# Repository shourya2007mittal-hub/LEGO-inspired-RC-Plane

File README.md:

# LEGO-inspired-RC-Plane

I made an single motor RC tailless aircraft with a custom flight controller based on STM32. It is based on STM32 and end design will be inspired by LEGO.

## Features

Microcontroller: STM32F401CBUx<br>
IMU Sensor: MPU-6050 <br>
Barometer: BMP280<br>
Design inspired by LEGO<br

 ## Schematic & PCB<br>

 # 3d Render<br>

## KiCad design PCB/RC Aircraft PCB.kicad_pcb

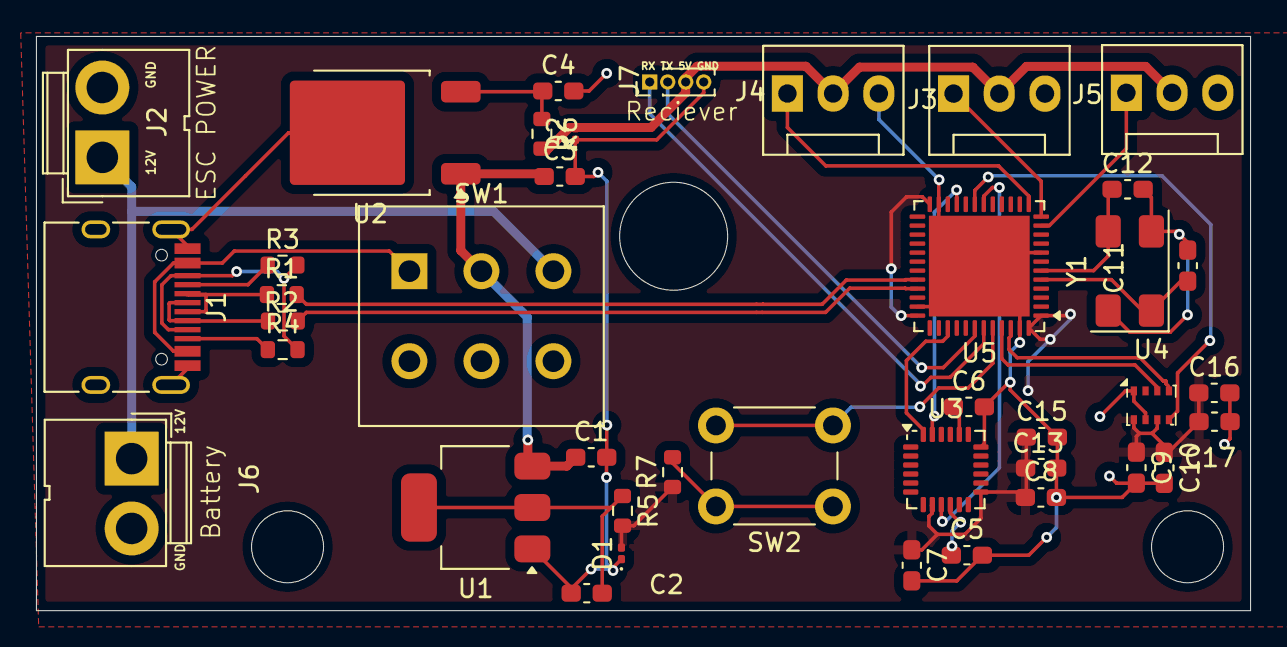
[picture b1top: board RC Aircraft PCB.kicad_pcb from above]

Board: 2 copper layers, 67.4 x 31.9 mm, 40 parts (0 on the bottom side), 32 nets.

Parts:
C1, C3, C7: 10 uf; C_0603_1608Metric_Pad1.08x0.95mm_HandSolder
C2, C4, C5, C8: 0.1uf; C_0603_1608Metric_Pad1.08x0.95mm_HandSolder
C6: 2.2 uf; C_0603_1608Metric_Pad1.08x0.95mm_HandSolder
C9, C10: 100nf; C_0603_1608Metric_Pad1.08x0.95mm_HandSolder
C11, C12: 12 pf; C_0603_1608Metric_Pad1.08x0.95mm_HandSolder
C13, C15, C16, C17: 100 pf; C_0603_1608Metric_Pad1.08x0.95mm_HandSolder
D1, D2: LED; LED_0201_0603Metric
J1: USB_C_Receptacle_USB2.0_16P; USB_C_Receptacle_HRO_TYPE-C-31-M-12
J2, J6: Conn_01x02_Pin; JWT_A3963_1x02_P3.96mm_Vertical
J3, J4, J5: Conn_01x03_Pin; FanPinHeader_1x03_P2.54mm_Vertical
J7: Conn_01x04_Pin; PinHeader_1x04_P1.00mm_Vertical
R1, R2: 33 R; R_0603_1608Metric
R3: 50 K; R_0603_1608Metric
R4: 50K; R_0603_1608Metric
R5, R6: 1k; R_0603_1608Metric
R7: 1 K; R_0603_1608Metric
SW1: SW_DPDT_x2; SW_PUSH_E-Switch_FS5700DP_DPDT
SW2: SW_Push; SW_PUSH_6mm
U1: AMS1117-3.3; SOT-223-3_TabPin2
U2: L7805; TO-252-2
U3: MPU-6050; InvenSense_QFN-24_4x4mm_P0.5mm
U4: BMP280; Bosch_LGA-8_2x2.5mm_P0.65mm_ClockwisePinNumbering
U5: STM32F401CBUx; QFN-48-1EP_7x7mm_P0.5mm_EP5.6x5.6mm
Y1: Crystal_GND24_Small; Crystal_SMD_0603-4Pin_6.0x3.5mm

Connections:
3.3V: C7.1, C8.1, C9.1, C10.1, C13.1, C15.1, C16.1, C17.1, D1.2 (A), R5.2, R7.1, U3.8 (VLOGIC), U3.13 (VDD), U4.6 (VDDIO), U4.8 (VDD), U5.1 (VBAT), U5.24 (VDD), U5.36 (VDD), U5.48 (VDD)
5V: D2.2 (A), J3.2, J4.2, J5.2, J7.3, R6.2
12 V: J2.1, J6.1, SW1.3 (C)
AD1: U3.9 (AD0), U5.18 (PB0)
AD2: U4.5 (SDO), U5.19 (PB1)
ESC: J5.1, U5.11 (PA1)
GND: C1.2, C2.2, C3.2, C4.2, C5.2, C6.2, C7.2, C8.2, C9.2, C10.2, C13.2, C15.2, C16.2, C17.2, D1.1 (K), D2.1 (K), J1.A1 (GND), J1.A8 (SBU1), J1.A12 (GND), J1.B1 (GND), J1.B8 (SBU2), J1.B12 (GND), J1.S1 (SHIELD), J2.2, J3.3, J4.3, J5.3, J6.2, J7.4, R3.2, R4.2, U1.1 (GND), U2.2 (GND), U3.18 (GND), U4.1 (GND), U4.7 (GND), U5.8 (VSSA), U5.23 (VSS), U5.35 (VSS), U5.47 (VSS), U5.49 (VSS)
unnamed: C11.2, C12.2, Y1.2 (G), Y1.4 (G)
unnamed: J1.A5 (CC1), R3.1
unnamed: J1.B5 (CC2), R4.1
unnamed: J1.A6 (D+), J1.B6 (D+), R2.1
unnamed: J1.A7 (D-), J1.B7 (D-), R1.1
unnamed: R7.2, SW2.1
unnamed: C2.1, R5.1, U1.2 (VO)
unnamed: C4.1, R6.1, U2.3 (OUT)
unnamed: C6.1, U3.20 (CPOUT)
unnamed: C5.1, U3.10 (REGOUT)
unnamed: SW2.2, U5.44 (BOOT0)
unnamed: C11.1, U5.5 (PH0), Y1.1
unnamed: C12.1, U5.6 (PH1), Y1.3
Power: C1.1, C3.1, SW1.2 (B), U1.3 (VI), U2.1 (IN)
RX: J7.1, U5.43 (PB7)
SCL: U3.23 (SCL), U5.21 (PB10)
SCL 2: U4.3 (SDI), U5.45 (PB8)
SDA: U3.24 (SDA), U5.39 (PB3)
SDA 2: U4.4 (SCK), U5.46 (PB9)
Servo_L: J3.1, U5.12 (PA2)
Servo_R: J4.1, U5.13 (PA3)
TX: J7.2, U5.42 (PB6)
USB 5V: J1.A4 (VBUS), J1.A9 (VBUS), J1.B4 (VBUS), J1.B9 (VBUS), SW1.1 (A)
_D+: R2.2, U5.33 (PA12)
_D-: R1.2, U5.32 (PA11)
